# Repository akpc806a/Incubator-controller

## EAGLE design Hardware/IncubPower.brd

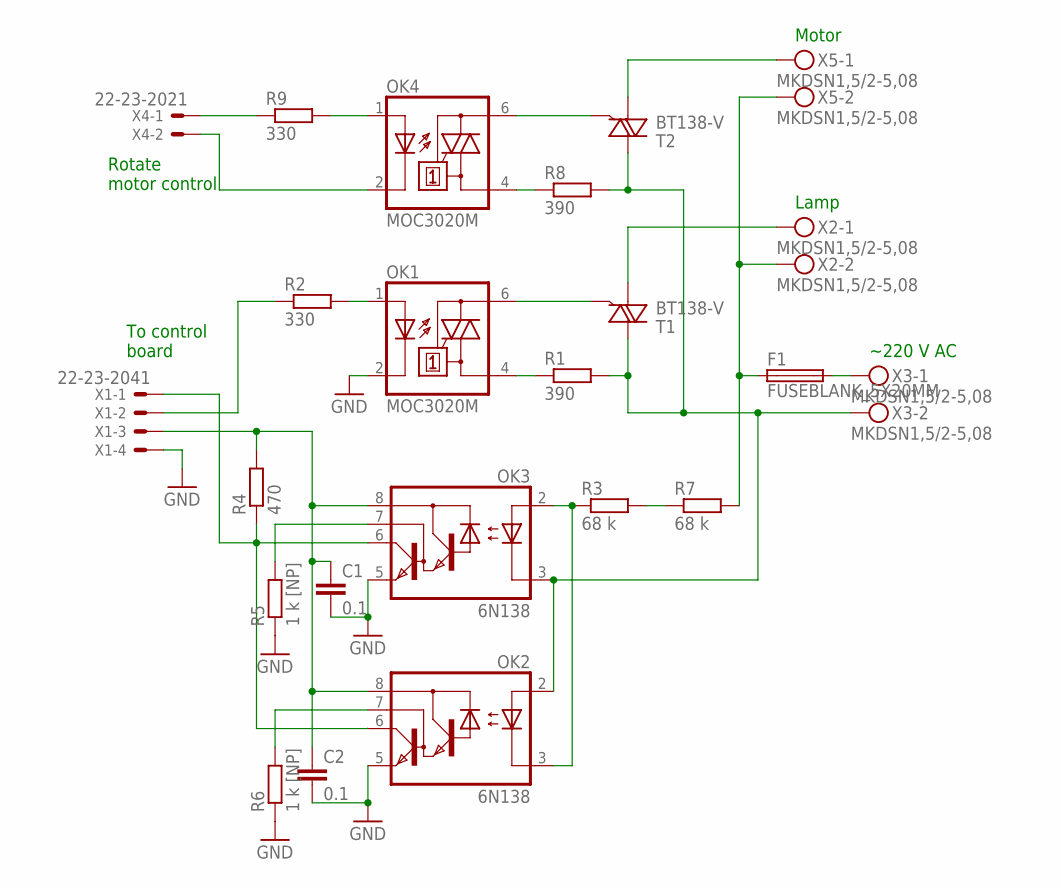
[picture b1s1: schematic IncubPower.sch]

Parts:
C1, C2: 0.1; C0805
F1: FUSEBLANK_5X20MM; FUSE_HOLDER_5X20MM
OK1, OK4: MOC3020M; DIL06
OK2, OK3: 6N138; DIL08
R1, R8: 390; 0204/7
R2, R9: 330; R0805
R3, R7: 68 k; 0204/7
R4: 470; R0805
R5, R6: 1 k [NP]; R0805
T1, T2: BT138-V; TO220BV
X1: 22-23-2041
X2, X3, X5: MKDSN1,5/2-5,08
X4: 22-23-2021

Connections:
GND: C1.2, C2.2, OK1.2 (C), OK2.5 (GND), OK3.5 (GND), R5.1, R6.1, X1.4
unnamed: OK1.6 (A2), T1.G
unnamed: OK1.4 (A1), R1.1
unnamed: T1.T1 (A1), X2.1
unnamed: OK1.1 (A), R2.2
unnamed: R2.1, X1.2
unnamed: C1.1, C2.1, OK2.8 (VCC), OK3.8 (VCC), R4.2, X1.3
unnamed: F1.1, R7.2, X2.2, X5.2
unnamed: OK2.2 (A), OK3.3 (C), R1.2, R8.2, T1.T2 (A2), T2.T2 (A2), X3.2
unnamed: F1.2, X3.1
unnamed: OK2.3 (C), OK3.2 (A), R3.1
unnamed: OK2.7 (VB), R6.2
unnamed: OK2.6 (VO), OK3.6 (VO), R4.1, X1.1
unnamed: OK3.7 (VB), R5.2
unnamed: R3.2, R7.1
unnamed: OK4.1 (A), R9.2
unnamed: R9.1, X4.1
unnamed: OK4.2 (C), X4.2
unnamed: OK4.6 (A2), T2.G
unnamed: OK4.4 (A1), R8.1
unnamed: T2.T1 (A1), X5.1

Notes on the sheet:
To control board
Lamp
~220 V AC
Rotate motor control
Motor

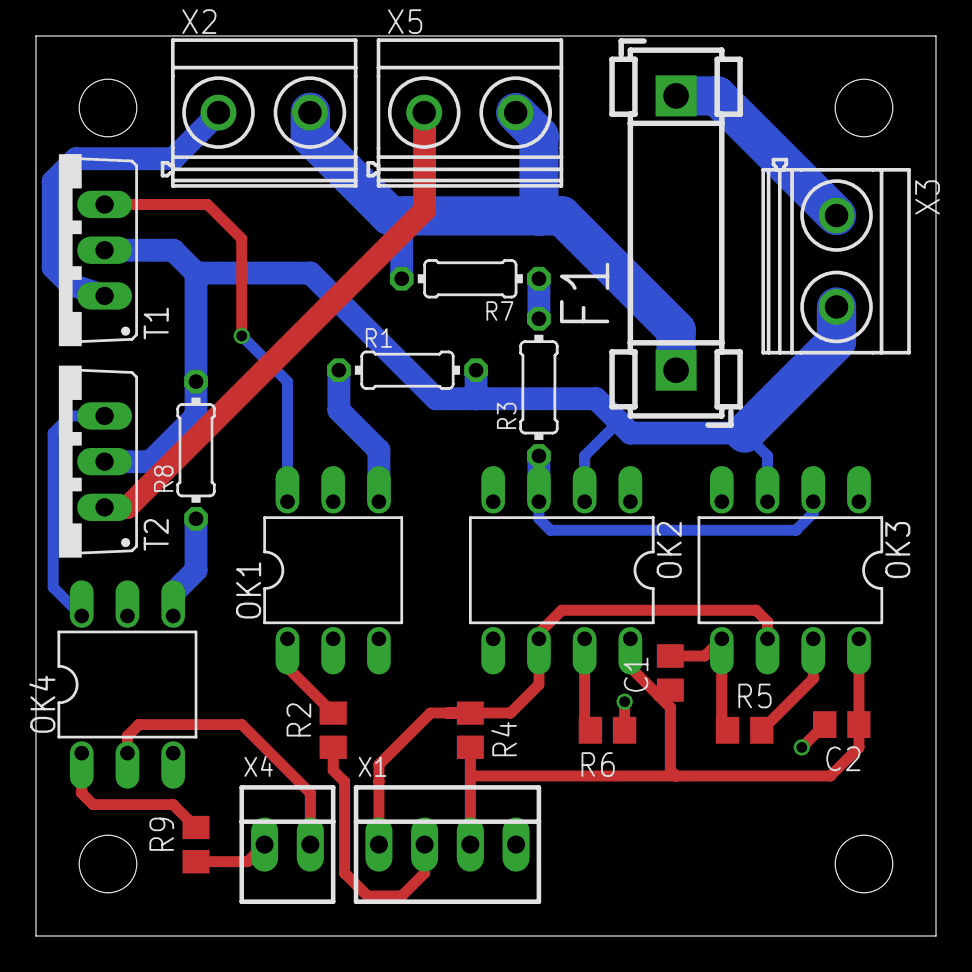
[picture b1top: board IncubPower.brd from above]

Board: 2 copper layers, 50.0 x 50.0 mm, 23 parts (0 on the bottom side), 21 nets.

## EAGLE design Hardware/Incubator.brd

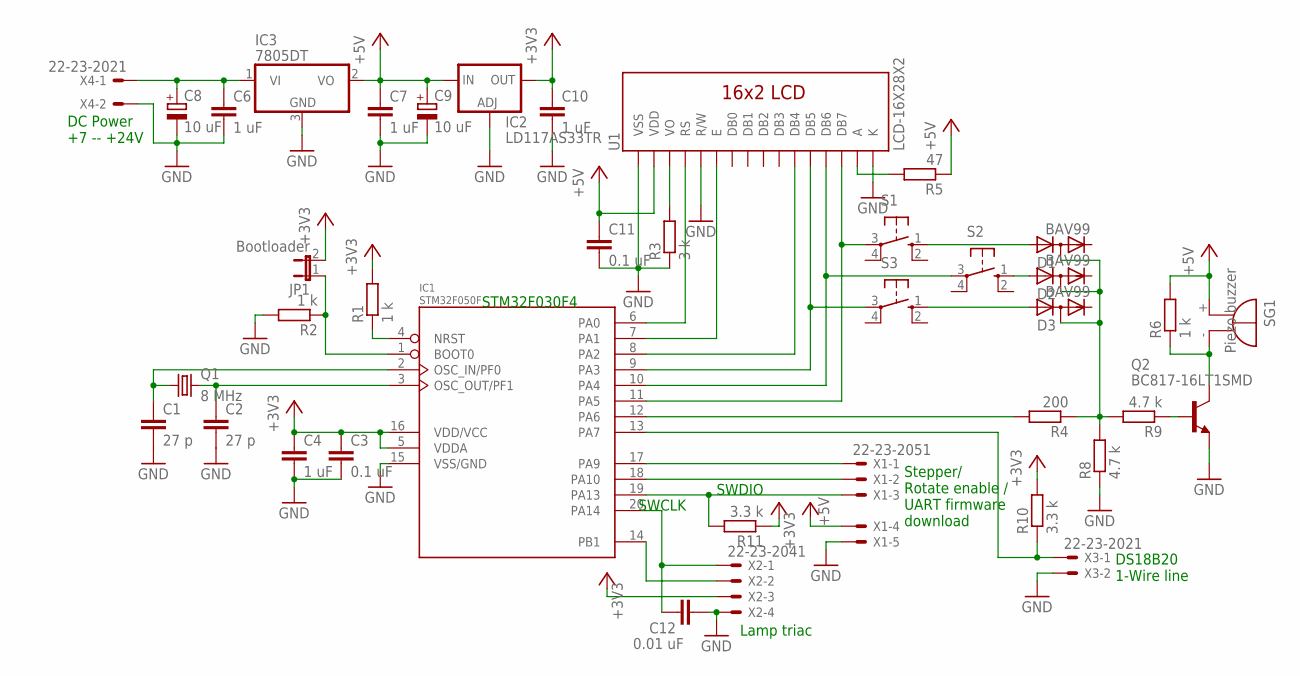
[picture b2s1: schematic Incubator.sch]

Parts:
C1, C2: 27 p; C0805
C3, C11: 0.1 uF; C0805
C4, C6, C7, C10: 1 uF; C0805
C8, C9: 10 uF; TT2D4L
C12: 0.01 uF; C0805
D1, D2, D3: BAV99; SOT23
IC1: STM32F050F; TSSOP20
IC2: LD117AS33TR; SOT223
IC3: 7805DT; TO252
JP1: Bootloader; JP1
Q1: 8 MHz; HC49/S
Q2: BC817-16LT1SMD; SOT23-BEC
R1, R2, R6: 1 k; R0805
R3: 3 k; R0805
R4: 200; R0805
R5: 47; R0805
R8, R9: 4.7 k; R0805
R10, R11: 3.3 k; R0805
S1, S2, S3: 10-XX; B3F-10XX
SG1: Piezo buzzer; F/HMB
U1: LCD-16X28X2; LCD-8X2
X1: 22-23-2051
X2: 22-23-2041
X3, X4: 22-23-2021

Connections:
+3V3: C3.1, C4.1, C10.1, IC1.5 (VDDA), IC1.16 (VDD/VCC), IC2.4 (OUT), JP1.2, R1.2, R10.2, R11.1, X2.3
+5V: C7.1, C9.+, C11.1, IC2.3 (IN), IC3.2 (VO), R5.1, R6.2, SG1.+, U1.2 (VDD), X1.4
GND: C1.2, C2.2, C3.2, C4.2, C6.2, C7.2, C8.-, C9.-, C10.2, C11.2, C12.2, IC1.15 (VSS/GND), IC2.1 (ADJ), IC3.3 (GND), Q2.E, R2.2, R3.1, R8.1, U1.1 (VSS), U1.5 (R/W), U1.16 (K), X1.5, X2.4, X3.2, X4.2
unnamed: C2.1, IC1.3 (OSC_OUT/PF1), Q1.2
unnamed: C1.1, IC1.2 (OSC_IN/PF0), Q1.1
unnamed: IC1.4 (NRST), R1.1
unnamed: IC1.1 (BOOT0), JP1.1, R2.1
unnamed: IC1.17 (PA9), X1.1
unnamed: IC1.18 (PA10), X1.2
unnamed: IC1.19 (PA13), R11.2, X1.3
unnamed: C12.1, IC1.20 (PA14), X2.1
unnamed: IC1.6 (PA0), U1.4 (RS)
unnamed: IC1.7 (PA1), U1.6 (E)
unnamed: IC1.8 (PA2), U1.11 (DB4)
unnamed: IC1.9 (PA3), S3.3, U1.12 (DB5)
unnamed: IC1.10 (PA4), S2.3, U1.13 (DB6)
unnamed: IC1.11 (PA5), S1.3, U1.14 (DB7)
unnamed: R3.2, U1.3 (VO)
unnamed: D1.3 (AC), D2.3 (AC), D3.3 (AC), R4.1, R8.2, R9.2
unnamed: D1.1 (A), S1.1 (S)
unnamed: D2.1 (A), S2.1 (S)
unnamed: D3.1 (A), S3.1 (S)
unnamed: Q2.B, R9.1
unnamed: Q2.C, R6.1, SG1.-
unnamed: IC1.14 (PB1), X2.2
unnamed: IC1.12 (PA6), R4.2
unnamed: IC1.13 (PA7), R10.1, X3.1
unnamed: C6.1, C8.+, IC3.1 (VI), X4.1
unnamed: R5.2, U1.15 (A)

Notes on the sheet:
Stepper/ Rotate enable / UART firmware download
DS18B20 1-Wire line
Lamp triac
DC Power +7 -- +24V
SWDIO
SWCLK
STM32F030F4

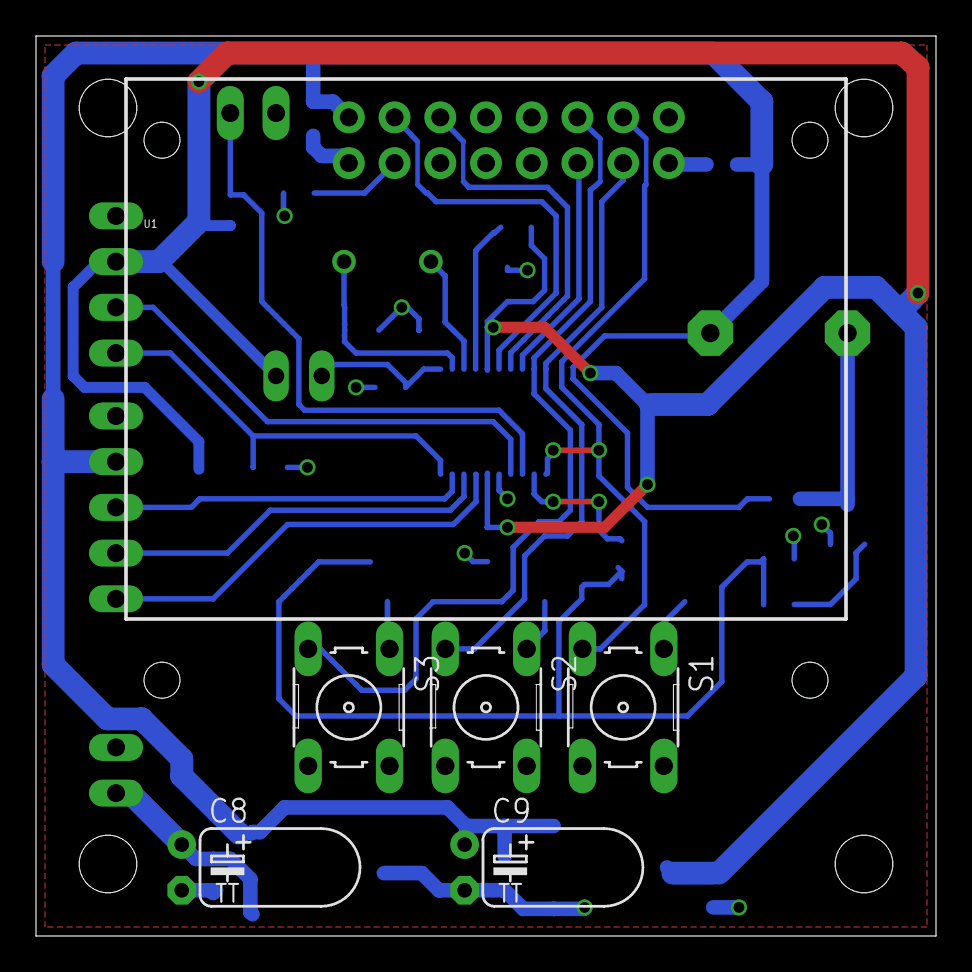
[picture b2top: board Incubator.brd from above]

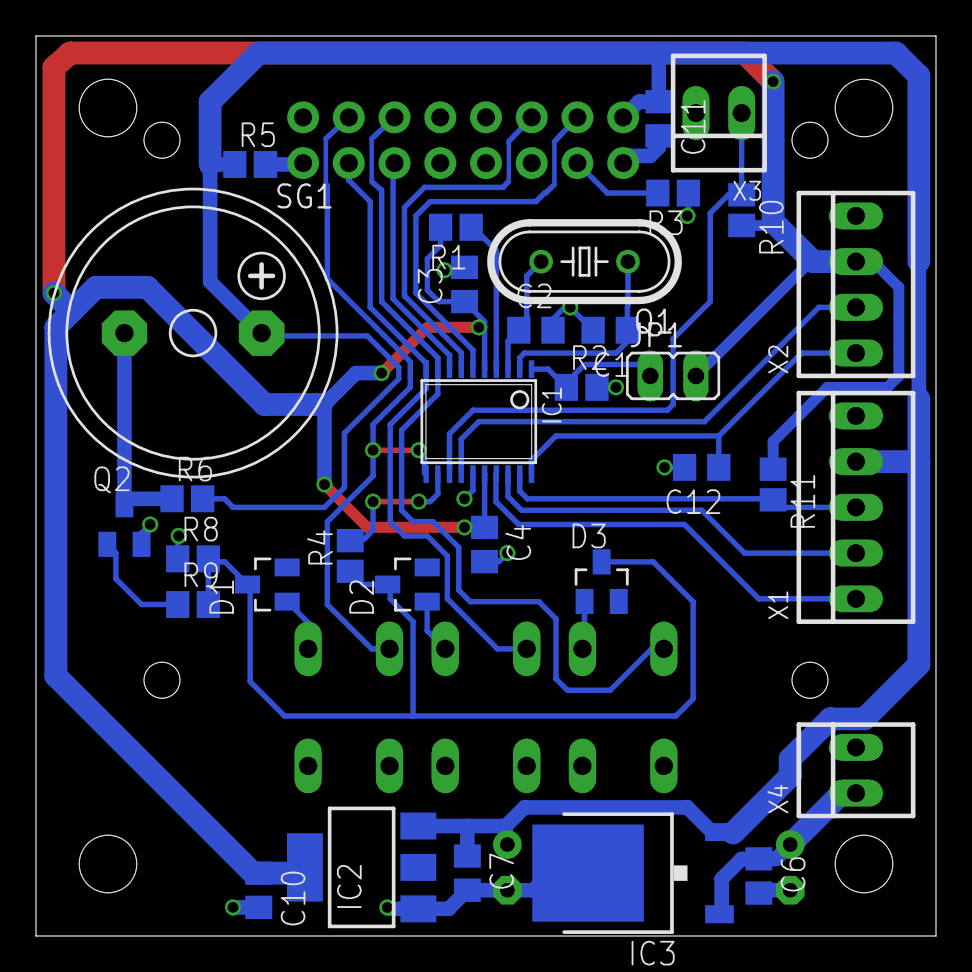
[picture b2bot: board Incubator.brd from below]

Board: 2 copper layers, 50.0 x 50.0 mm, 39 parts (33 on the bottom side), 29 nets.

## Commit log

2014-09-14 :space_invader: Added .gitattributes & .gitignore files
2014-09-14 Initial version
    - Hardware: ordered at DirtyPCBs
    - Firmware: tested at STM32F0308-Discovery board
2014-11-02 Release version
    Version for production
    - 3 buttons on control board
2014-11-02 Firmware update
    Last firmware for new hardware

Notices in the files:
parts and their libraries:
SparkFun-Displays: Licensing: Creative Commons ShareAlike 4.0 International - https://creativecommons.org/licenses/by-sa/4.0
